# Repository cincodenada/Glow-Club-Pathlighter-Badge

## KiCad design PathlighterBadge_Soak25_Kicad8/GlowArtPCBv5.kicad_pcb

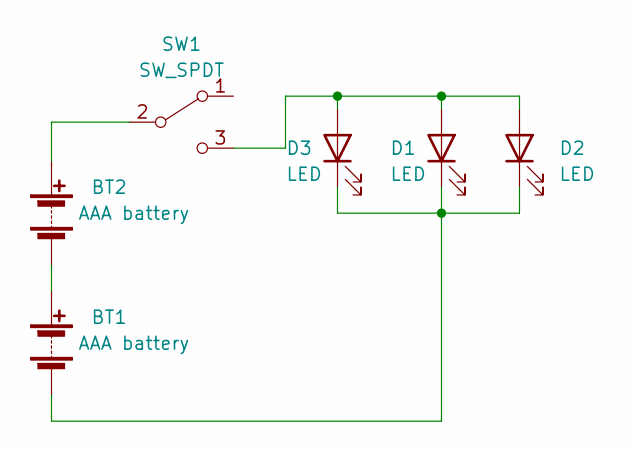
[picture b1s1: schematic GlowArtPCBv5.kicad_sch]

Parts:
BT1, BT2: AAA battery; BatteryHolder_Keystone_2466_1xAAA
D1, D2, D3: LED; LED_D5.0mm_Horizontal_O1.27mm_Z3.0mm
SW1: SW_SPDT; SW_MHSS1105_SPST_Angled

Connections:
unnamed: BT1.1 (+), BT2.2 (-)
unnamed: BT1.2 (-), D1.1 (K), D2.1 (K), D3.1 (K)
unnamed: BT2.1 (+), SW1.2 (B)
unnamed: D1.2 (A), D2.2 (A), D3.2 (A), SW1.3 (C)

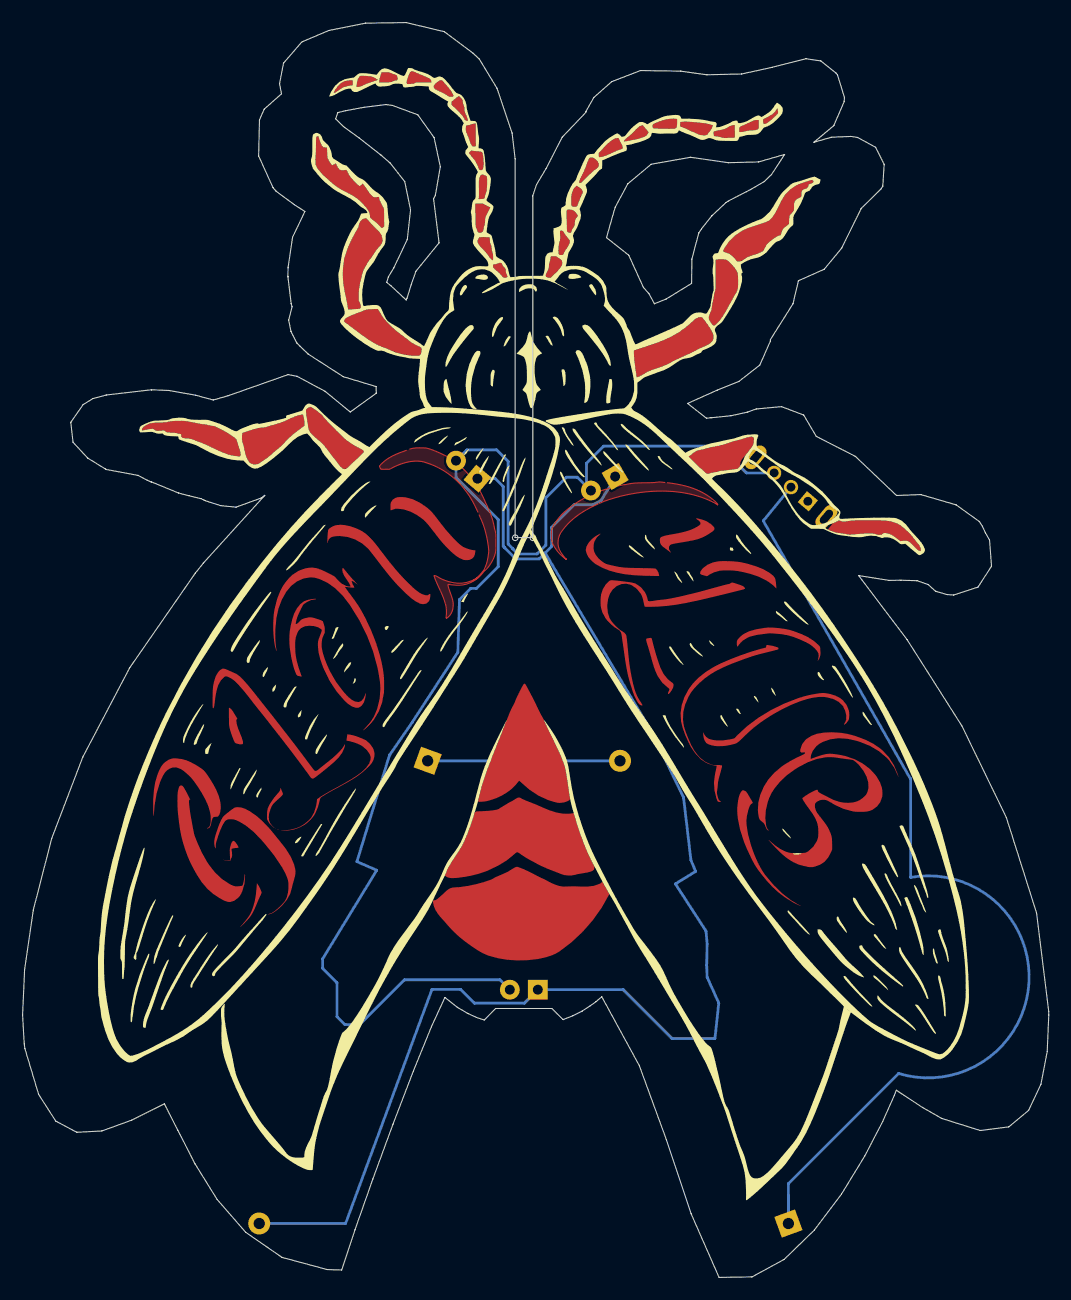
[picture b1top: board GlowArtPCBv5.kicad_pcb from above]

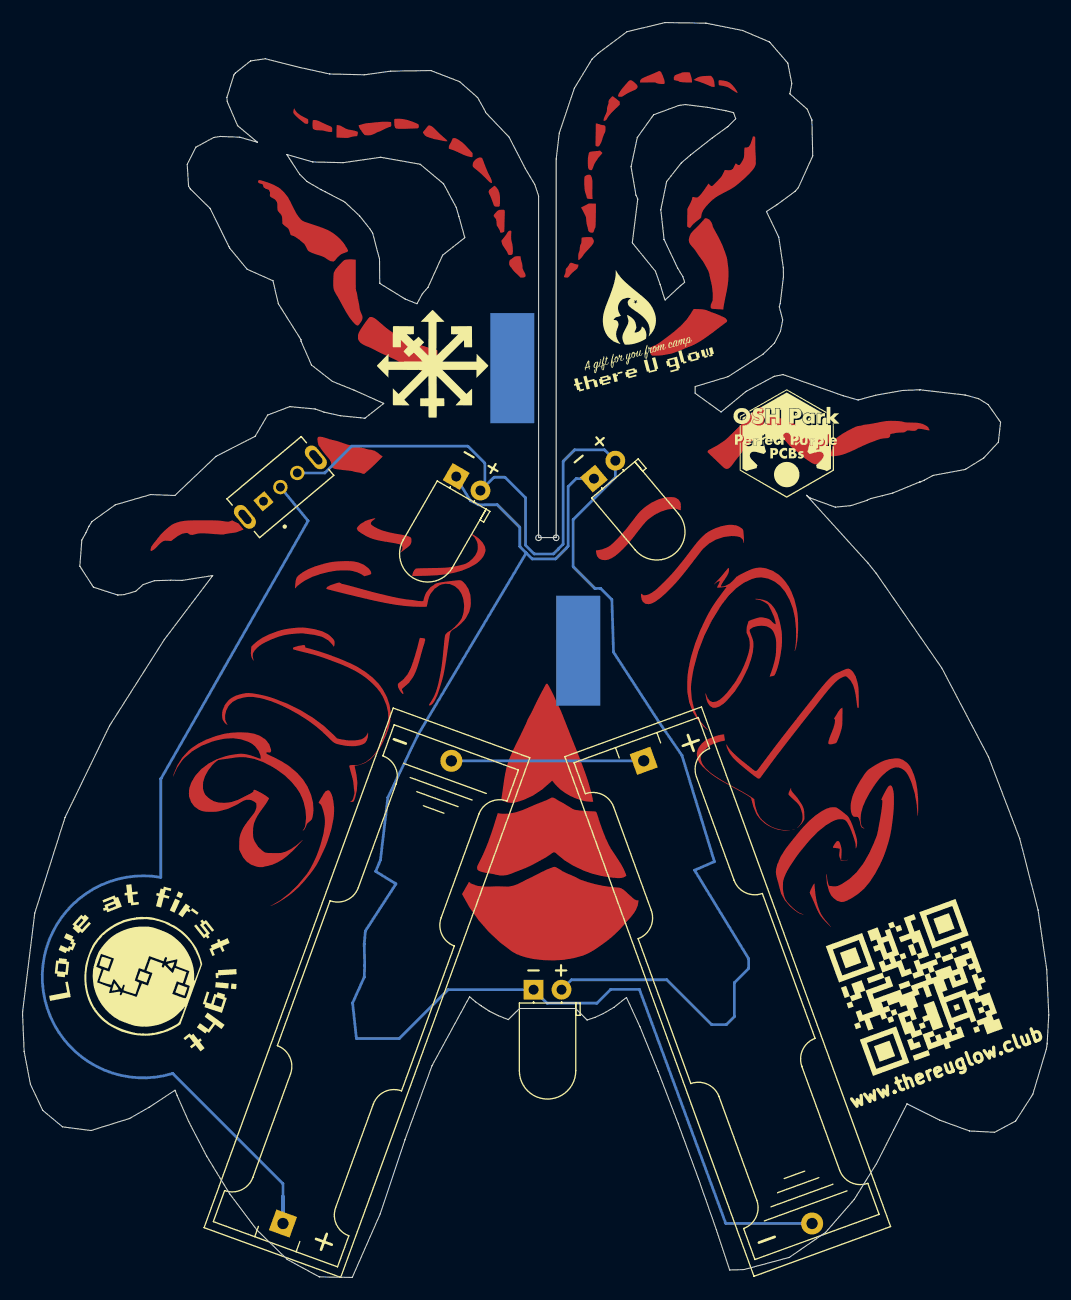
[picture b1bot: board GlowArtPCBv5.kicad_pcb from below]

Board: 2 copper layers, 93.2 x 113.9 mm, 7 parts (6 on the bottom side), 4 nets.

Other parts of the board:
B1: BugBackbone

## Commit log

2025-03-08 Initial setup for v5 badge
2025-03-12 Add SVGs and update board
2025-03-13 Remove hole struts
2025-03-13 Add simplified version of bug vector
2025-03-13 Join the butt, some editorial bits
2025-03-13 Re-split butt
2025-03-13 Separate wings
2025-03-13 Start moving things to layers
2025-03-13 Split and group everything
2025-03-13 Move everything to layers
2025-03-13 Add holes and shrink
    Why was this just slightly wrong??
2025-03-13 Remove old design
2025-03-13 Update for V1
2025-03-13 Add font
2025-03-13 Add silkscreen text
2025-03-13 Adjust board outline alignment
2025-03-13 More logos from old board
2025-04-04 Start building 3D pcb
2025-04-04 Add footprints
2025-04-18 Scootch backbone?
2025-04-23 Final OSHPark version
2025-04-25 Flip slots again, move logos
    Slot's gotta be this way so there's room for the LED
2025-04-25 Rework backbone
2025-05-07 Tweaks from feedback
2025-05-08 Fix overlap on G/C, adjust backbone bands
2025-05-08 Final tweaks, hopefully!
2025-05-08 Lots of little tweaks getting ready for production
    Rerouting traces, baking board outlines without the weird bits,
    adding silkscreen bits, generally polishing
2025-05-08 Fix Edge.Cuts on backbone
2025-05-08 More final tweaks of some sort
